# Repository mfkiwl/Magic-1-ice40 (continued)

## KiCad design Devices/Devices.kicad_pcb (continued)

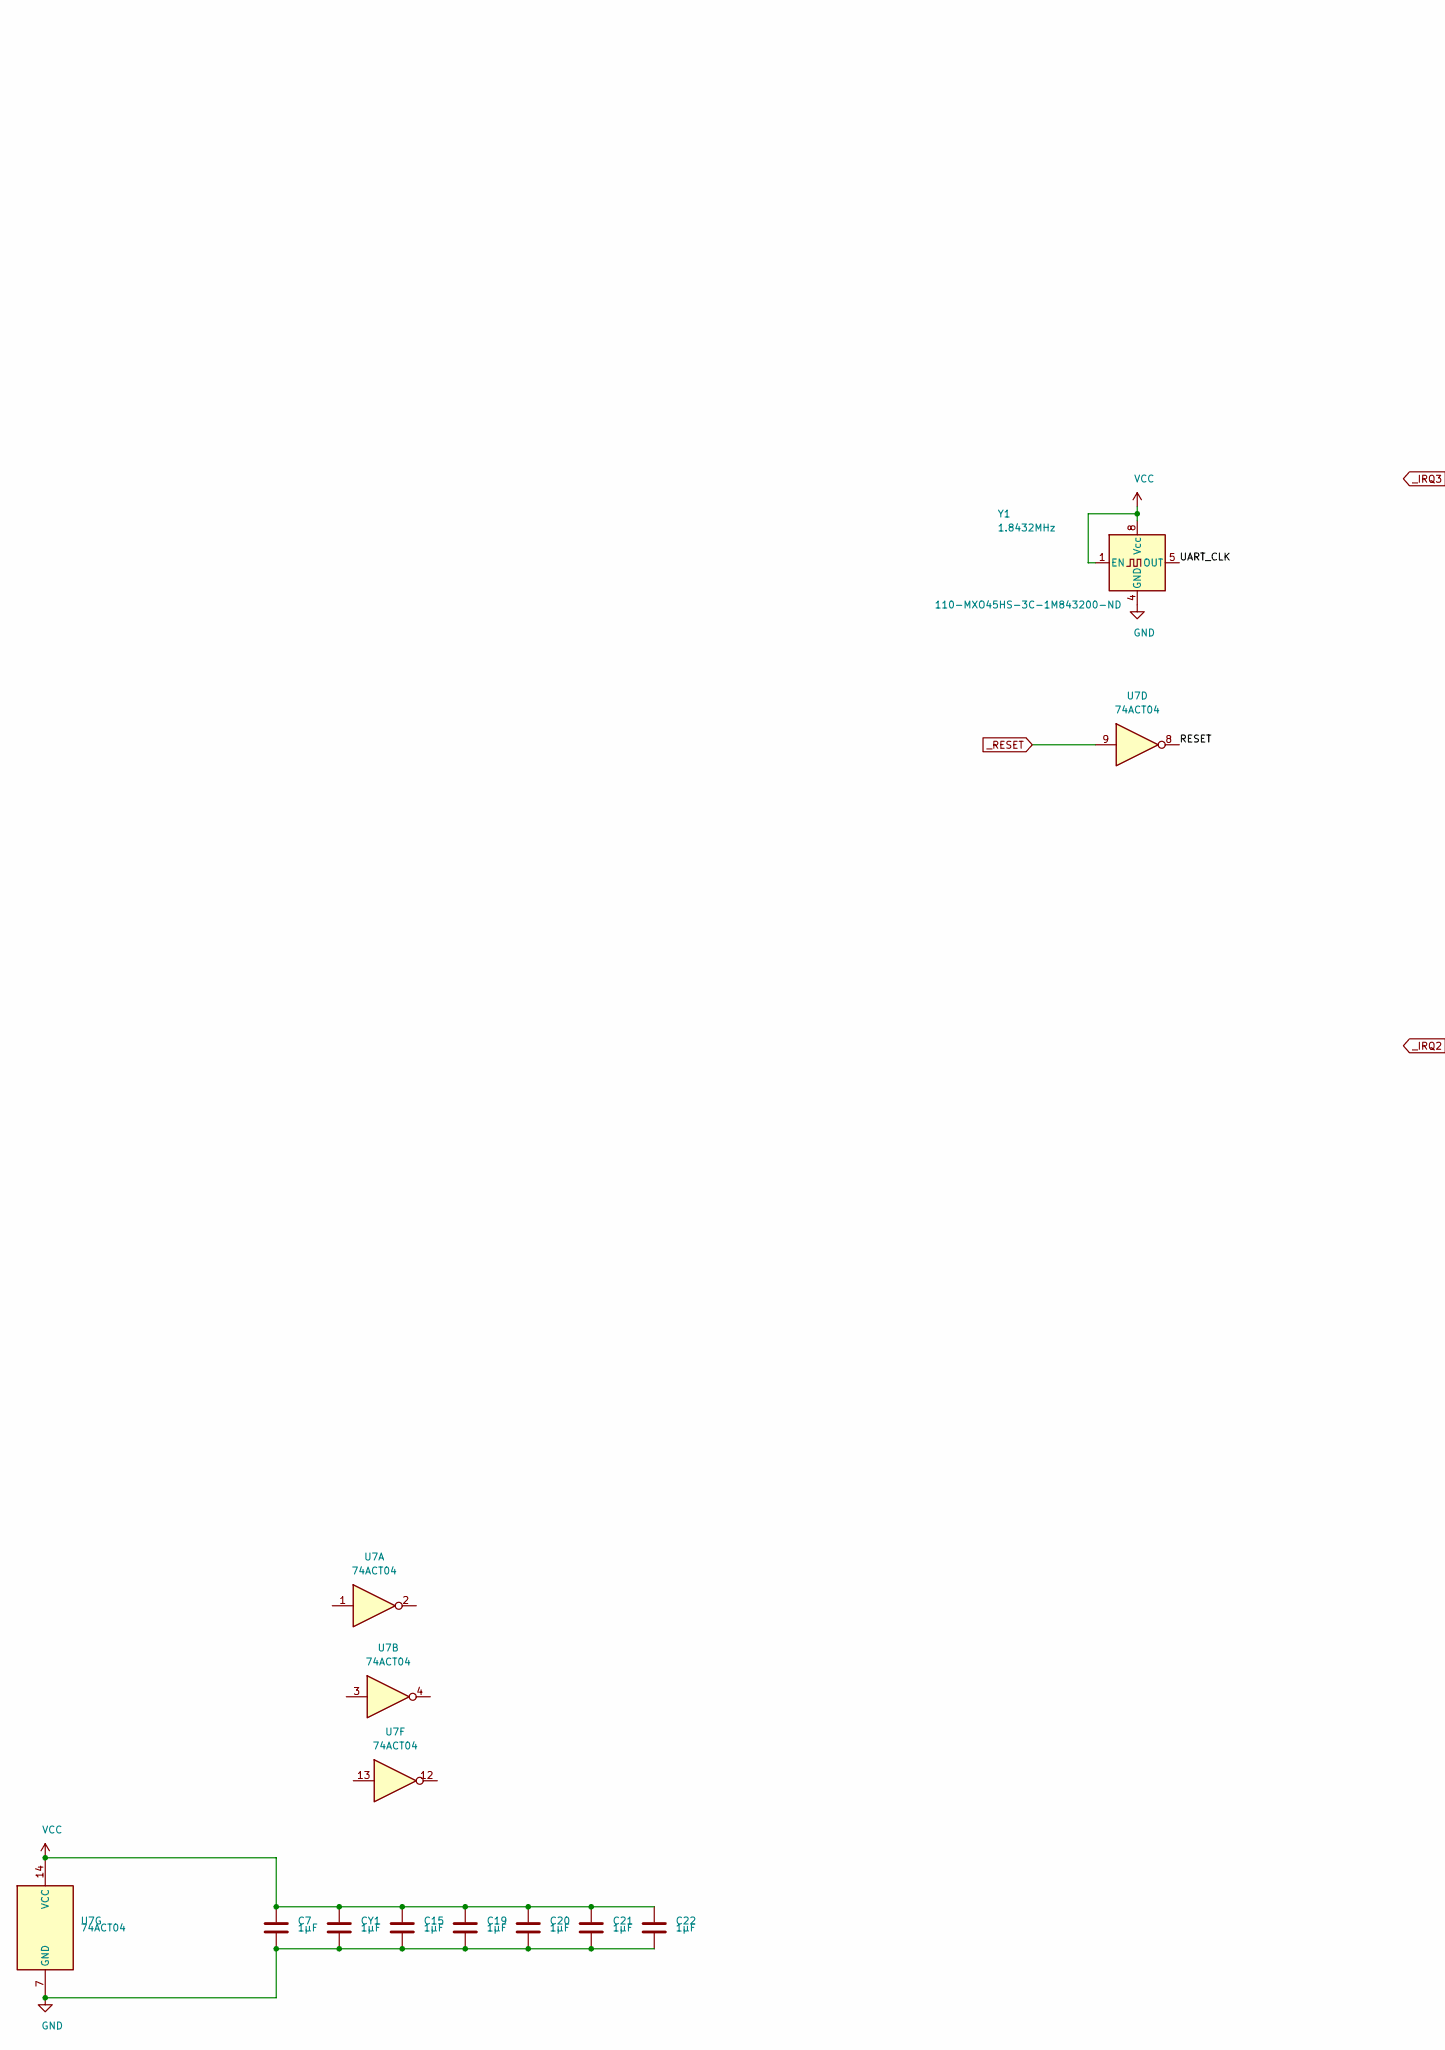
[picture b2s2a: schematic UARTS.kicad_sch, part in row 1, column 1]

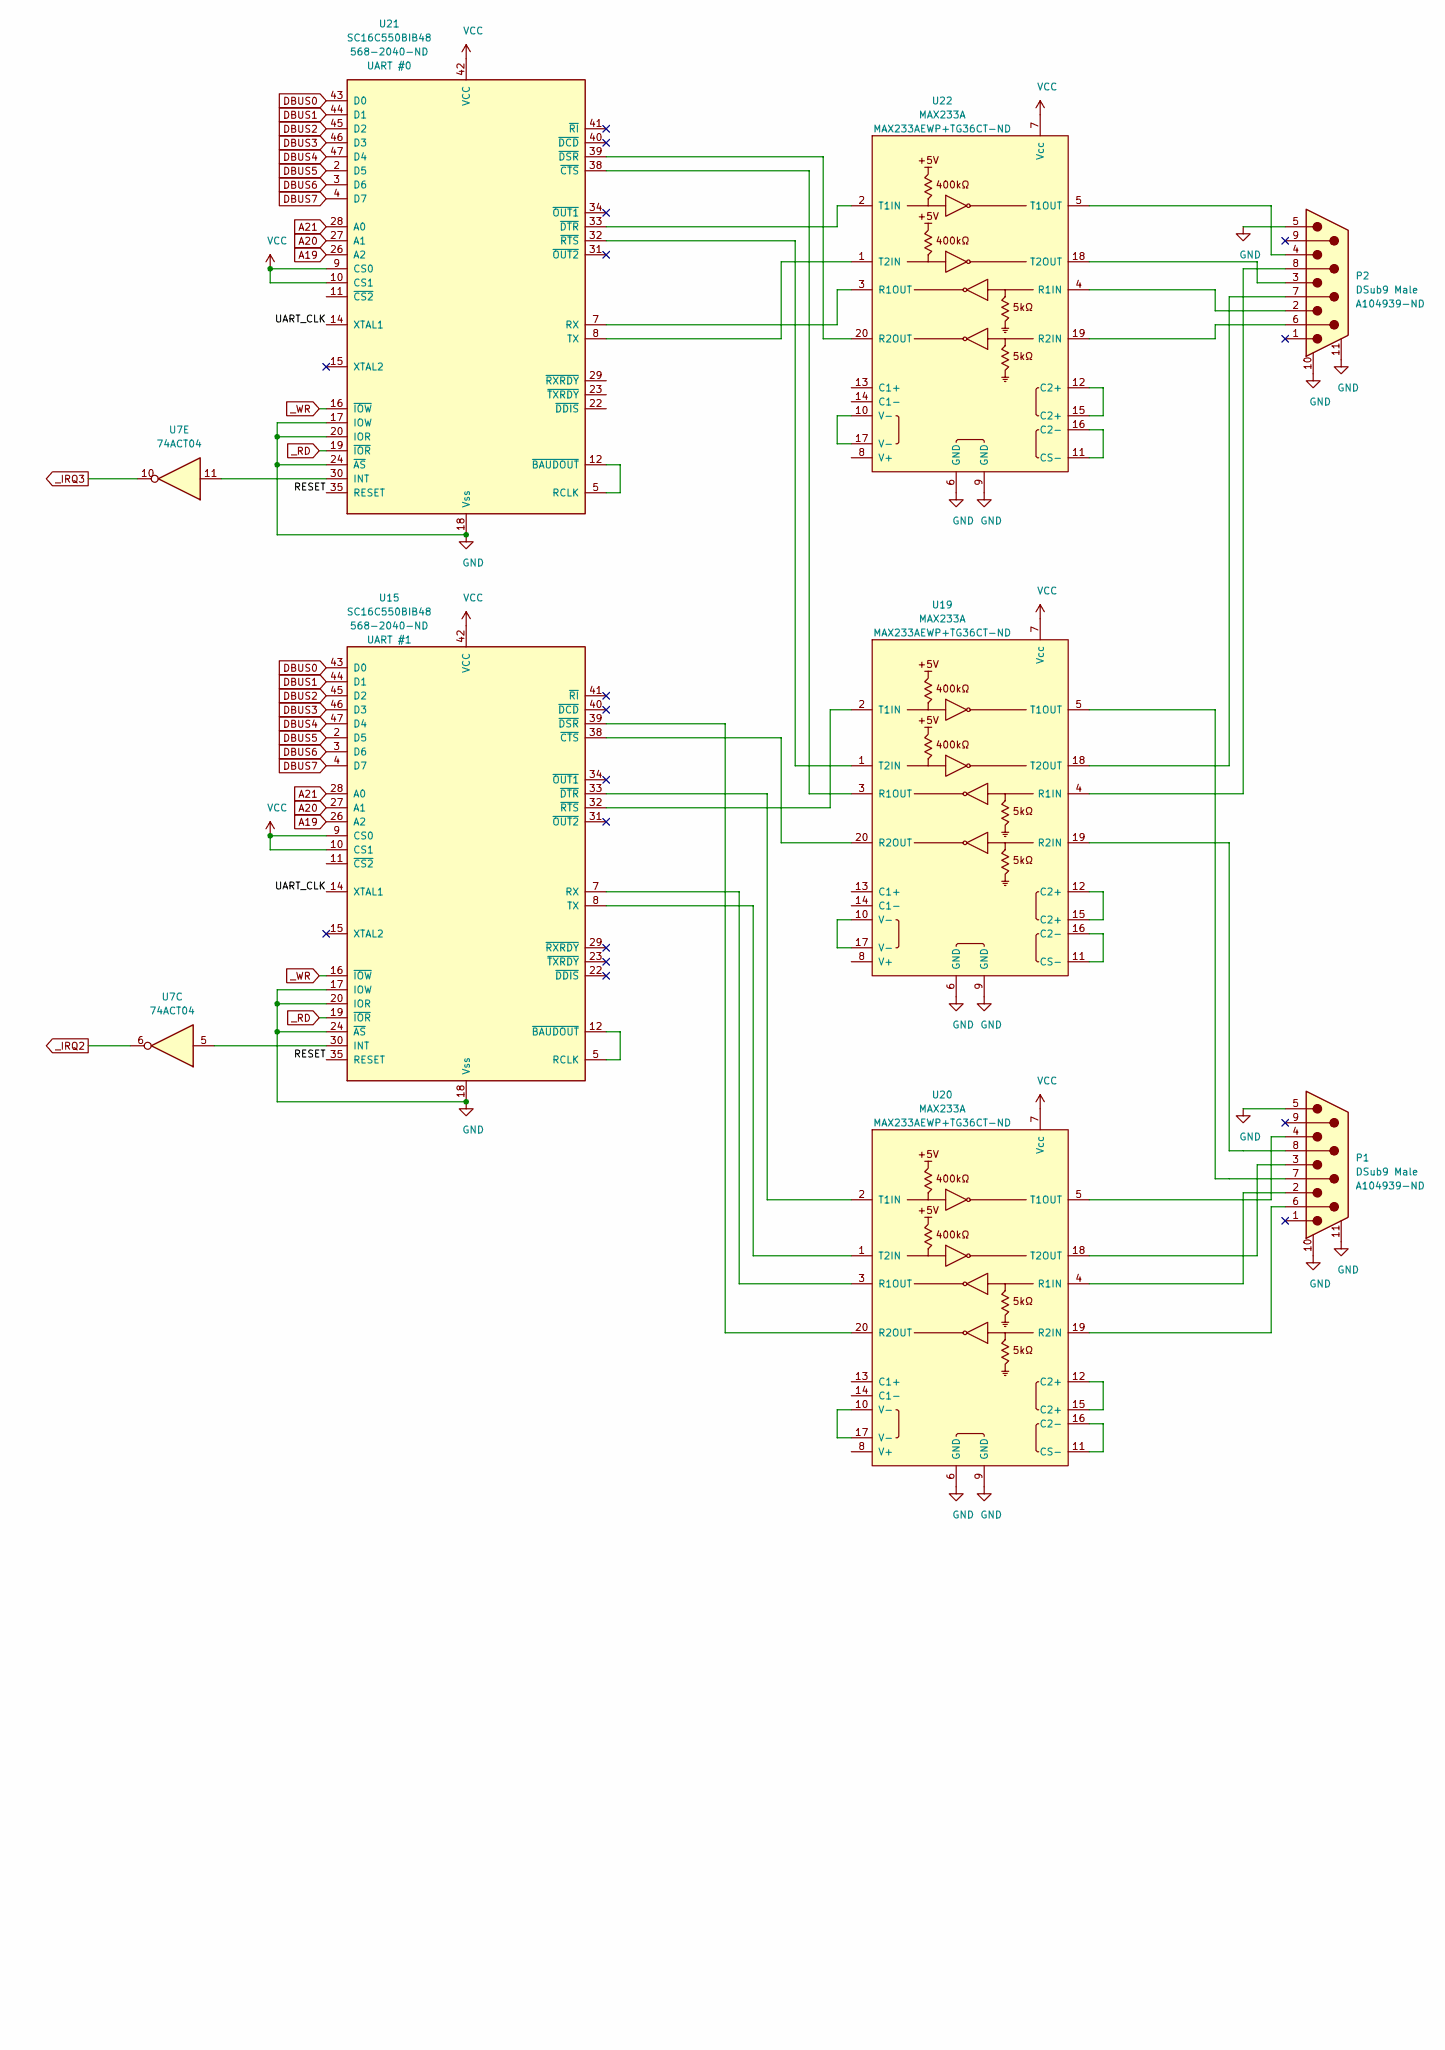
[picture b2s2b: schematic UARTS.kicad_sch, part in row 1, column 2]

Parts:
C7, C15, C19, C20, C21, C22: 1µF; C_1206_3216Metric
CY1: 1µF; C_1206_3216Metric
P1, P2: DSub9 Male; DSUB9_1393481-5; Digikey A104939-ND
U7: 74ACT04; SOIC-14_3.9x8.7mm_P1.27mm
U15, U21: SC16C550BIB48; LQFP-48_7x7mm_P0.5mm; Digikey 568-2040-ND
U19, U20, U22: MAX233A; SOIC-20W_7.5x12.8mm_P1.27mm; Digikey MAX233AEWP+TG36CT-ND
Y1: 1.8432MHz; Oscillator_DIP-8; Digikey 110-MXO45HS-3C-1M843200-ND

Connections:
/UARTS/A19: U15.26 (A2), U21.26 (A2)
/UARTS/A20: U15.27 (A1), U21.27 (A1)
/UARTS/A21: U15.28 (A0), U21.28 (A0)
/UARTS/DBUS0: U15.43 (D0), U21.43 (D0)
/UARTS/DBUS1: U15.44 (D1), U21.44 (D1)
/UARTS/DBUS2: U15.45 (D2), U21.45 (D2)
/UARTS/DBUS3: U15.46 (D3), U21.46 (D3)
/UARTS/DBUS4: U15.47 (D4), U21.47 (D4)
/UARTS/DBUS5: U15.2 (D5), U21.2 (D5)
/UARTS/DBUS6: U15.3 (D6), U21.3 (D6)
/UARTS/DBUS7: U15.4 (D7), U21.4 (D7)
/UARTS/RESET: U7.8, U15.35 (RESET), U21.35 (RESET)
/UARTS/UART_CLK: U15.14 (XTAL1), U21.14 (XTAL1), Y1.5 (OUT)
GND: C7.2, C15.2, C19.2, C20.2, C21.2, C22.2, CY1.2, P1.5, P1.10 (PAD), P1.11 (PAD), P2.5, P2.10 (PAD), P2.11 (PAD), U7.7 (GND), U15.17 (IOW), U15.18 (Vss), U15.20 (IOR), U15.24 (~AS~), U19.6 (GND), U19.9 (GND), U20.6 (GND), U20.9 (GND), U21.17 (IOW), U21.18 (Vss), U21.20 (IOR), U21.24 (~AS~), U22.6 (GND), U22.9 (GND), Y1.4 (GND)
unnamed: P1.2, U20.4 (R1IN)
unnamed: P1.3, U20.18 (T2OUT)
unnamed: P1.4, U20.5 (T1OUT)
unnamed: P1.6, U20.19 (R2IN)
unnamed: P1.7, U19.5 (T1OUT)
unnamed: P1.8, U19.19 (R2IN)
unnamed: P2.2, U22.4 (R1IN)
unnamed: P2.3, U22.18 (T2OUT)
unnamed: P2.4, U22.5 (T1OUT)
unnamed: P2.6, U22.19 (R2IN)
unnamed: P2.7, U19.18 (T2OUT)
unnamed: P2.8, U19.4 (R1IN)
unnamed: U15.7 (RX), U20.3 (R1OUT)
unnamed: U15.8 (TX), U20.1 (T2IN)
unnamed: U15.5 (RCLK), U15.12 (~BAUDOUT~)
unnamed: U7.5, U15.30 (INT)
unnamed: U15.32 (~RTS~), U19.2 (T1IN)
unnamed: U15.33 (~DTR~), U20.2 (T1IN)
unnamed: U15.38 (~CTS~), U19.20 (R2OUT)
unnamed: U15.39 (~DSR~), U20.20 (R2OUT)
unnamed: U19.1 (T2IN), U21.32 (~RTS~)
unnamed: U19.3 (R1OUT), U21.38 (~CTS~)
unnamed: U19.10 (V-), U19.17 (V-)
unnamed: U19.11 (CS-), U19.16 (C2-)
unnamed: U19.12 (C2+), U19.15 (C2+)
unnamed: U20.10 (V-), U20.17 (V-)
unnamed: U20.11 (CS-), U20.16 (C2-)
unnamed: U20.12 (C2+), U20.15 (C2+)
unnamed: U21.7 (RX), U22.3 (R1OUT)
unnamed: U21.8 (TX), U22.1 (T2IN)
unnamed: U21.5 (RCLK), U21.12 (~BAUDOUT~)
unnamed: U7.11, U21.30 (INT)
unnamed: U21.33 (~DTR~), U22.2 (T1IN)
unnamed: U21.39 (~DSR~), U22.20 (R2OUT)
unnamed: U22.10 (V-), U22.17 (V-)
unnamed: U22.11 (CS-), U22.16 (C2-)
unnamed: U22.12 (C2+), U22.15 (C2+)
VCC: C7.1, C15.1, C19.1, C20.1, C21.1, C22.1, CY1.1, U7.14 (VCC), U15.9 (CS0), U15.10 (CS1), U15.42 (VCC), U19.7 (Vcc), U20.7 (Vcc), U21.9 (CS0), U21.10 (CS1), U21.42 (VCC), U22.7 (Vcc), Y1.1 (EN), Y1.8 (Vcc)
_IRQ2: U7.6
_IRQ3: U7.10
_RD: U15.19 (~IOR~), U21.19 (~IOR~)
_RESET: U7.9
_WR: U15.16 (~IOW~), U21.16 (~IOW~)

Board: 2 copper layers, 16 parts (0 on the bottom side), 54 nets, no tracks yet.

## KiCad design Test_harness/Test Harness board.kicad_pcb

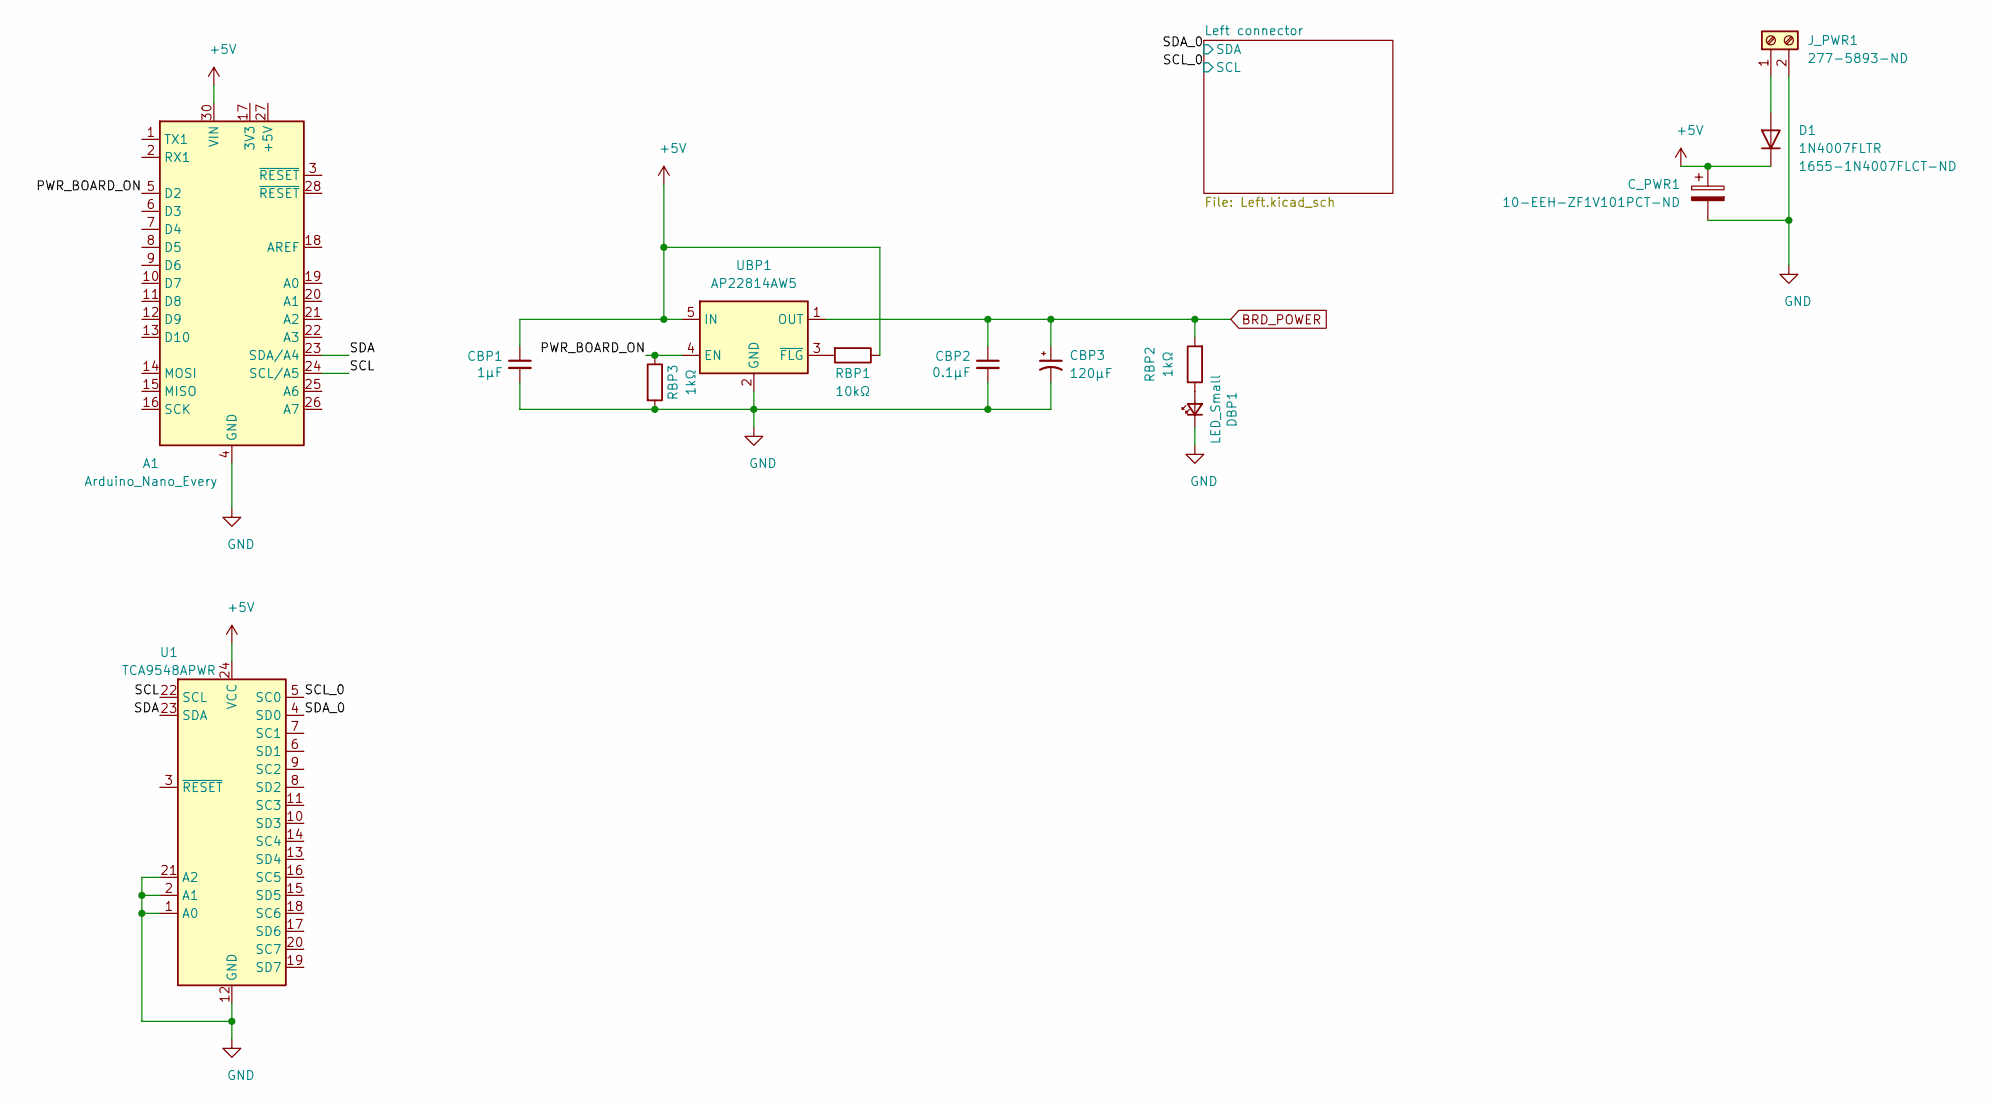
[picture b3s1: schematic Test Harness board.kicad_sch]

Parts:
A1: Arduino_Nano_Every; Arduino_Nano
CBP1: 1µF; C_0805_2012Metric
CBP2: 0.1µF; C_0805_2012Metric
CBP3: 120µF; CP_Elec_6.3x9.9
C_PWR1: CP; CP_Elec_8x10; Digikey 10-EEH-ZF1V101PCT-ND
D1: 1N4007FLTR; D_SOD-123F; Digikey 1655-1N4007FLCT-ND
DBP1: LED_Small; LED_0805_2012Metric; Digikey 160-1167-1-ND
J_PWR1: Screw_Terminal_01x02; TerminalBlock_Phoenix_MKDS-1,5-2-5.08_1x02_P5.08mm_Horizont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; Digikey 277-5893-ND
RBP1: 10kΩ; R_0805_2012Metric
RBP2, RBP3: 1kΩ; R_0805_2012Metric
U1: TCA9548APWR; TSSOP-24_4.4x7.8mm_P0.65mm
UBP1: AP22814AW5; SOT-23-5

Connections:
+5V: A1.30 (VIN), CBP1.1, C_PWR1.1, D1.1 (K), RBP1.1, U1.24 (VCC), UBP1.5 (IN); also elsewhere on the board
/PWR_BOARD_ON: A1.5 (D2), RBP3.1, UBP1.4 (EN)
/SCL: A1.24 (SCL/A5), U1.22 (SCL)
/SCL_0: U1.5 (SC0); also elsewhere on the board
/SDA: A1.23 (SDA/A4), U1.23 (SDA)
/SDA_0: U1.4 (SD0); also elsewhere on the board
BRD_POWER: CBP2.1, CBP3.1, RBP2.2, UBP1.1 (OUT); also elsewhere on the board
GND: A1.4 (GND), A1.29 (GND), CBP1.2, CBP2.2, CBP3.2, C_PWR1.2, DBP1.1 (K), J_PWR1.2, RBP3.2, U1.1 (A0), U1.2 (A1), U1.12 (GND), U1.21 (A2), UBP1.2 (GND); also elsewhere on the board
unnamed: D1.2 (A), J_PWR1.1
unnamed: DBP1.2 (A), RBP2.1
unnamed: RBP1.2, UBP1.3 (~FLG)
